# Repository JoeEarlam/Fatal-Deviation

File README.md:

# Fatal Deviation

Fatal Deviation is my 1.5KG beetleweight lifter, with independent 4WD and electronic stability control. The name comes from Ireland's first full-length martial arts movie of the same name, which can be found in its entirety on youtube for the morbidly curious.

This repository is not intended to be instructional - this isn't a full open-source project, but a reference for myself and others who want to see how the sausage is made. If you do build your own (or something similar), please let me know, I'd love to see more weird tiny beetleweights on the scene!

For more information on the design and build process, please check out my build thread: https://forum.bristolbotbuilders.com/t/fatal-deviation-my-over-engineered-beetleweight/232

TPU front end, the night before Bristol Bot Builders' Summer Showdown, July 2025

Steel front end, for Robodojo, May 2025

## Design Criteria and Overview

I impulse bought a TIG welder in Lidl and needed more excuses to use it. Somebody on the internet said that it wasn't possible to build a somewhat competitive beetleweight robot almost entirely from steel. Together, that was all the motivation I needed. Watching fast lifter/grappler bots like P1, Whiplash, Claw Viper/Red Storm, and having previous experience racing RC cars, I knew how I wanted the bot to drive - fast, agile, predictable. This gave me some design requirements:

* Extremely compact chassis to allow as much armour coverage as possible.
* Four independently controlled drive motors, for redundancy and torque vectoring.
* Small, compact and powerful lifter mechanism.
* As much RGB as possible while still having enough power left over for the bot to drive.

## Mechanical Design

The mechanical design uses a welded 304 stainless steel chassis tub - 2mm sides and bottom, with 4mm front and rear sections. Stainless was chosen for aesthetic reasons, and because 2mm hardox is very difficult to source.

The wedge is soft-mounted via threaded aluminium inserts pressed into TPU brackets. The tub protects a TPU clamshell that sandwiches the internal components together, via long screws and threaded inserts to pull it together. Self-tapping screws are used to hold the clamshell into the chassis tub which suspends all the internal components and hopefully provides some shock absorption.

The TPU clamshell design means all the internal components of the robot can be removed as a unit for repair on the bench. Accessing any component only takes a couple of minutes, although unfortunately due to the compact design many connections have to be soldered rather than connectorised/

## Electronic Design

The only way to cram electronics into the remaining space inside the bot is to integrate every function (aside from the receiver) into a single PCB. In approximately 50x70mm total board area, the PCB provides:

* Seeed Xiao RP2040 microcontroller
* 4x 6A drive channels (TI DRV8256P drivers), with current sensing.
* MPU6050 gyro + accelerometer
* IBUS receiver compatible
* Servo power and signal pads
* 7x WS2812 RGB LEDs

The four layer PCB was designed with heavy usage of copper pours, optimised to keep resistance (both electrical and thermal) and inductance as low as possible when using cheap 1oz copper fabrication processes (2oz often costs 3-4 as much as 1oz!). The design also keeps the hot and EMI-prone motor drivers and servo power pads far away from the sensitive IMU and MCU. While only supposed to run 2-3 minutes at a time for events, it's been stress tested with 5-10 minutes of continuous running and barely rises over 45c, even with no airflow and four hot motors spinning inside the bot.

## Software Design

The software is written in Arduino IDE, utilising both cores of the RP2040 microcontroller. The firmware uses the wonderful [TaskScheduler](https://github.com/arkhipenko/TaskScheduler) library by arkhipenko to handle timing and looping, with modularity provided by custom classes containing motor driver logic, IMU data processing, and drive maths. The task-based asynchronous code allows predictable timing for data acquisition and filter functions, while also optimising for minimum latency by triggering drive maths routines the instant that a new radio packet is received.

IMU gyroscope data is used, in combination with the steering channel data received from the RC transmitter, as the input and target variables of a PID loop, which provides the electronic stability control - the bot will steer to self correct back to its intended course if disrupted; either by a bump in the floor or contact with another robot, and allows the bot to hold dead straight line acceleration or smooth drifts on low-friction surfaces where it would otherwise spin out uncontrollably. To improve the turning radius (which is otherwise somewhat poor due to the long aspect ratio of the bot) the front inside wheel is braked on sharp turns, while the rear inside wheel coasts, shifting the centre of rotation for the bot forwards.

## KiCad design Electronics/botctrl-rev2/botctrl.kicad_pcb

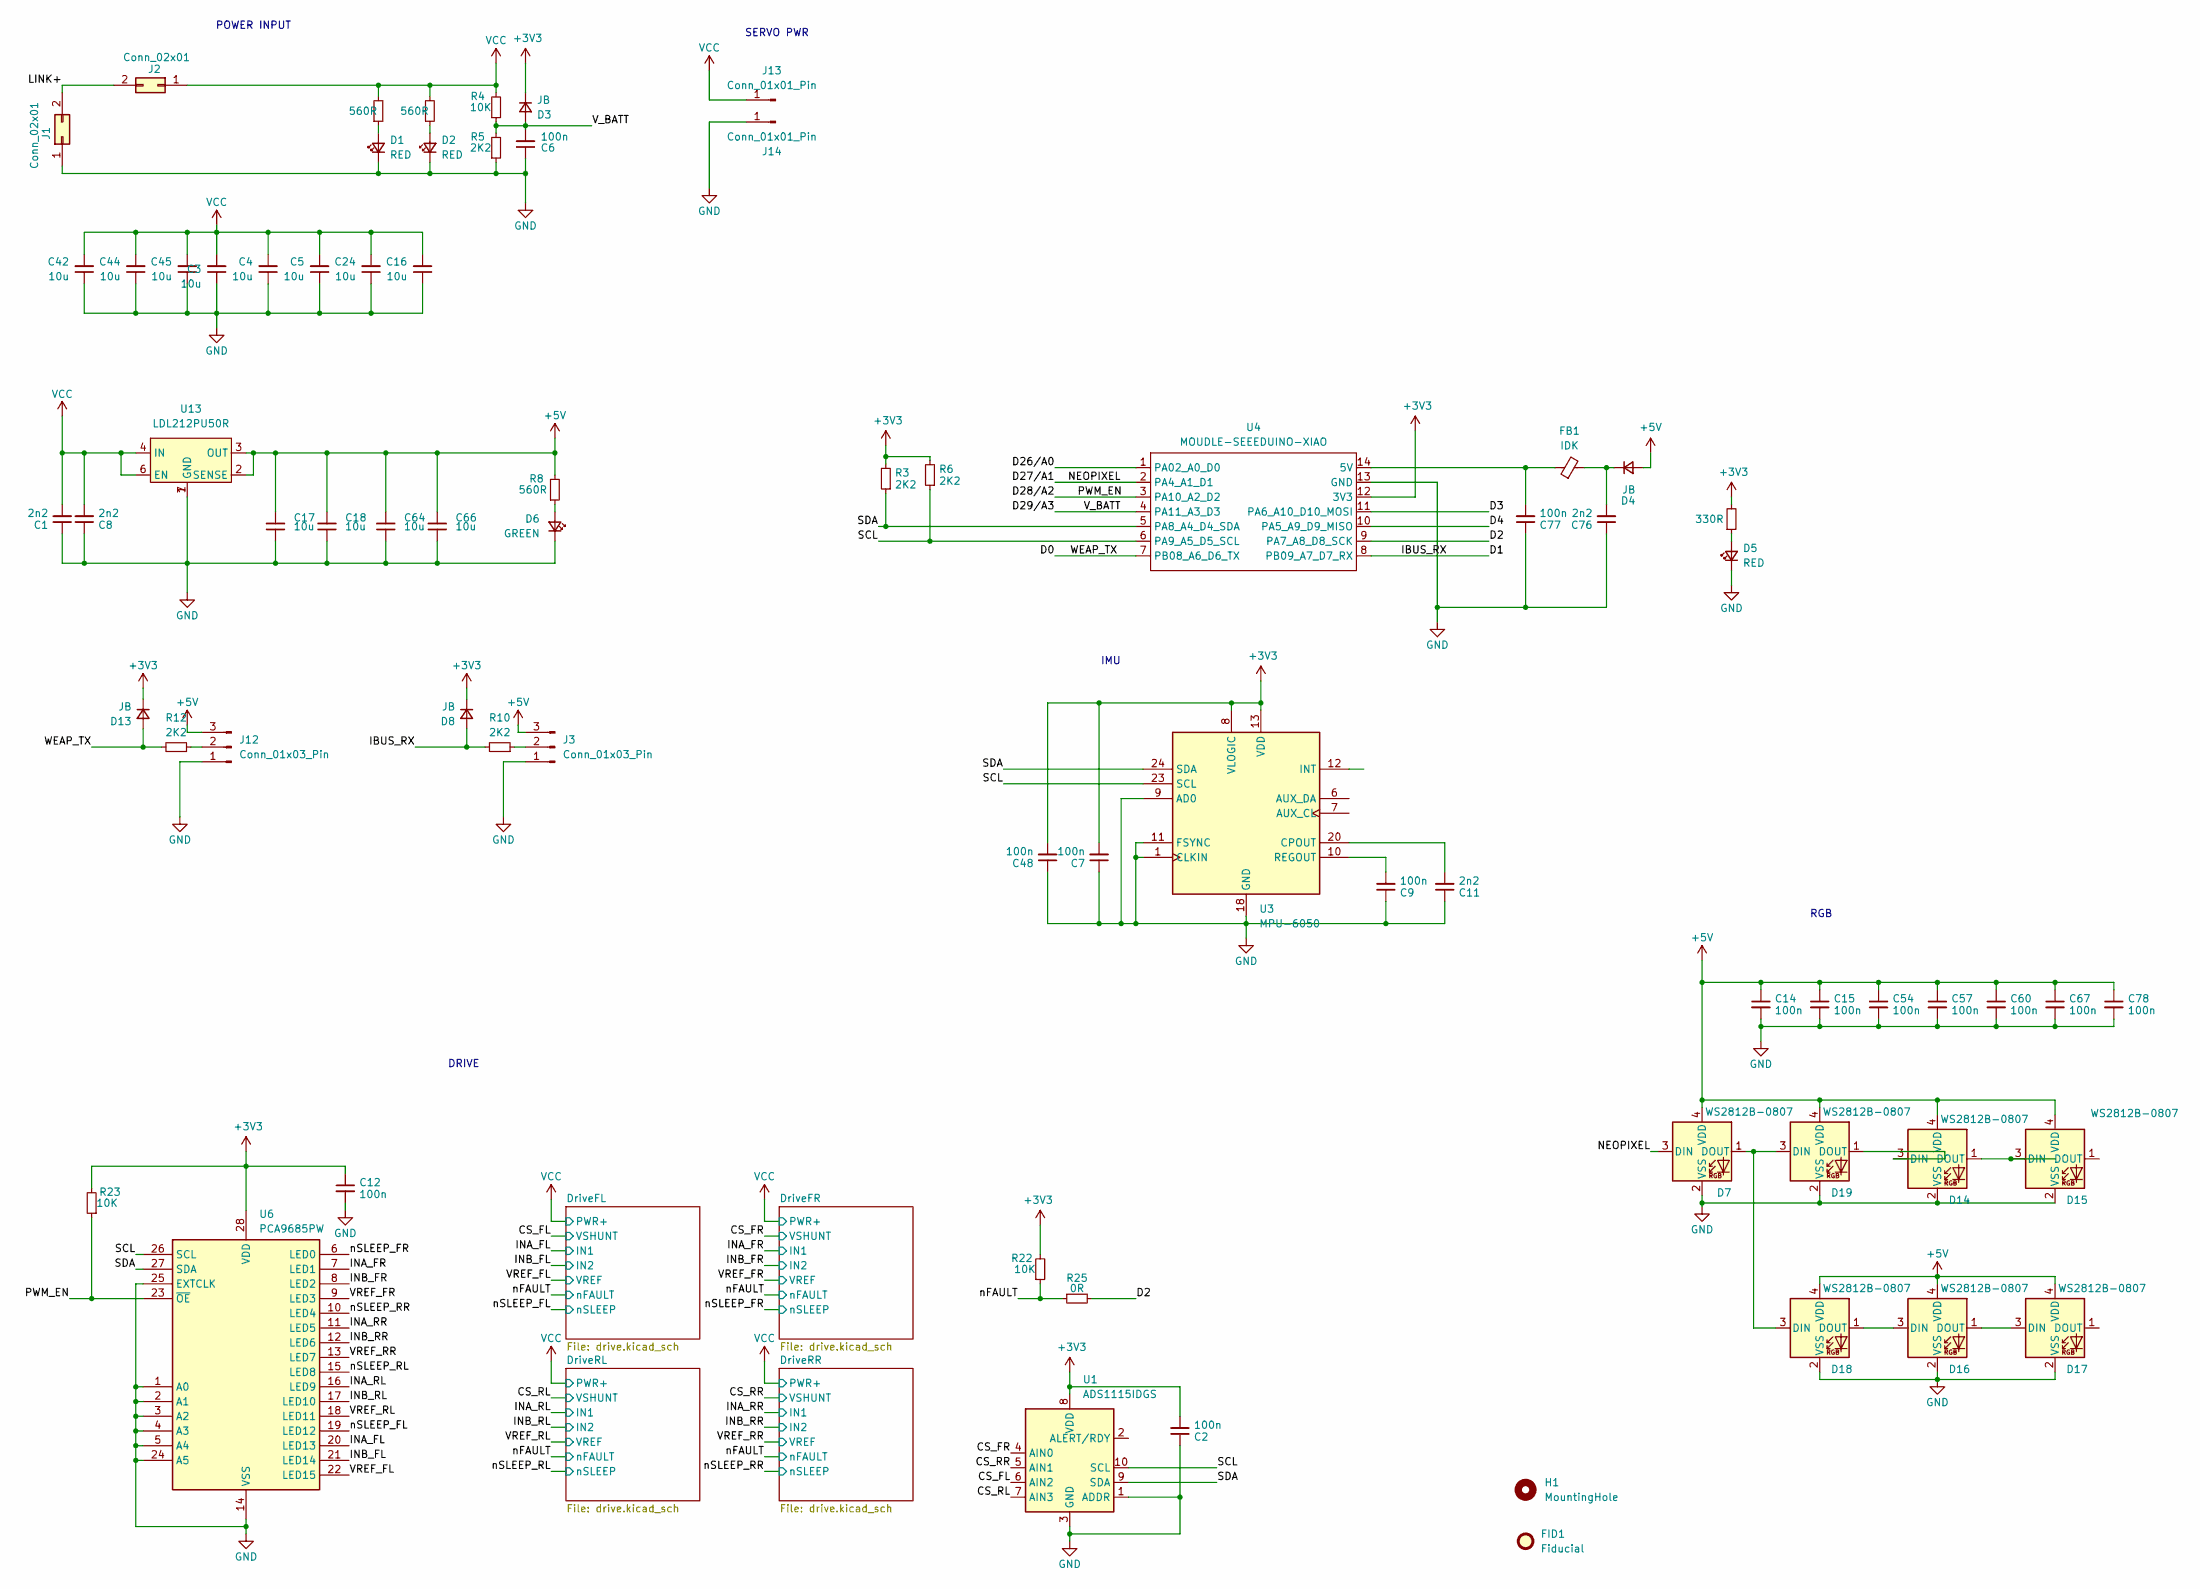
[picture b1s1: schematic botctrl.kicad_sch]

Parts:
C1, C8, C11, C76: 2n2; C_0603_1608Metric
C2, C6, C7, C9, C12, C14, C15, C48, C54, C57, C60, C67, C77, C78: 100n; C_0603_1608Metric
C3, C4, C5, C16, C17, C18, C24, C42, C44, C45, C64, C66: 10u; C_1206_3216Metric
D1, D2: RED; LED_Kingbright_APFA3010_3x1.5mm_Horizontal
D3, D4, D8, D13: JB; D_0603_1608Metric
D5: RED; D_0603_1608Metric
D6: GREEN; D_0603_1608Metric
D7, D14, D15, D16, D17, D18, D19: WS2812B-0807; WS2812-0807
FB1: IDK; L_0603_1608Metric; Part Number 0R
FID1: Fiducial; el-botto
H1: MountingHole; MountingHole_4.3mm_M4_DIN965
J1, J2: Conn_02x01; SolderWire-0.75sqmm_1x02_P4.8mm_D1.25mm_OD2.3mm
J3, J12: Conn_01x03_Pin; SolderWire-0.127sqmm_1x03_P3.7mm_D0.48mm_OD1mm
J13, J14: Conn_01x01_Pin; SolderWire-0.25sqmm_1x01_D0.65mm_OD1.7mm
R1, R2, R8: 560R; R_0603_1608Metric
R3, R5, R6, R10, R12: 2K2; R_0603_1608Metric
R4, R22, R23: 10K; R_0603_1608Metric
R7: 330R; R_0603_1608Metric
R25: 0R; R_0603_1608Metric
U1: ADS1115IDGS; TSSOP-10_3x3mm_P0.5mm
U3: MPU-6050; InvenSense_QFN-24_4x4mm_P0.5mm
U4: MOUDLE-SEEEDUINO-XIAO; MOUDLE14P-SMD-2.54-21X17.8MM
U6: PCA9685PW; TSSOP-28_4.4x9.7mm_P0.65mm
U13: LDL212PU50R; DFN-6-1EP_3x3mm_P0.95mm_EP1.7x2.6mm

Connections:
+3V3: C2.2, C7.2, C12.1, C48.2, D3.1 (K), D8.1 (K), D13.1 (K), R3.2, R6.2, R7.2, R22.2, R23.2, U1.8 (VDD), U3.8 (VLOGIC), U3.13 (VDD), U4.12 (3V3), U6.28 (VDD)
+5V: C14.1, C15.1, C17.2, C18.2, C54.1, C57.1, C60.1, C64.2, C66.2, C67.1, C78.1, D4.2 (A), D7.4 (VDD), D14.4 (VDD), D15.4 (VDD), D16.4 (VDD), D17.4 (VDD), D18.4 (VDD), D19.4 (VDD), J3.3, J12.3, R8.2, U13.2 (SENSE), U13.3 (OUT)
/CS_FL: U1.6 (AIN2); also elsewhere on the board
/CS_FR: U1.4 (AIN0); also elsewhere on the board
/CS_RL: U1.7 (AIN3); also elsewhere on the board
/CS_RR: U1.5 (AIN1); also elsewhere on the board
/D0: D13.2 (A), R12.2, U4.7 (PB08_A6_D6_TX)
/D1: D8.2 (A), R10.2, U4.8 (PB09_A7_D7_RX)
/D2: R25.2, U4.9 (PA7_A8_D8_SCK)
/D3: U4.11 (PA6_A10_D10_MOSI)
/D4: U4.10 (PA5_A9_D9_MISO)
/D26/A0: U4.1 (PA02_A0_D0)
/D27/A1: D7.3 (DIN), U4.2 (PA4_A1_D1)
/D28/A2: R23.1, U4.3 (PA10_A2_D2), U6.23 (~OE)
/D29/A3: C6.2, D3.2 (A), R4.1, R5.2, U4.4 (PA11_A3_D3)
/INA_FL: U6.20 (LED13); also elsewhere on the board
/INA_FR: U6.7 (LED1); also elsewhere on the board
/INA_RL: U6.16 (LED9); also elsewhere on the board
/INA_RR: U6.11 (LED5); also elsewhere on the board
/INB_FL: U6.21 (LED14); also elsewhere on the board
/INB_FR: U6.8 (LED2); also elsewhere on the board
/INB_RL: U6.17 (LED10); also elsewhere on the board
/INB_RR: U6.12 (LED6); also elsewhere on the board
/LINK+: J1.2, J2.2
/SCL: R6.1, U1.10 (SCL), U3.23 (SCL), U4.6 (PA9_A5_D5_SCL), U6.26 (SCL)
/SDA: R3.1, U1.9 (SDA), U3.24 (SDA), U4.5 (PA8_A4_D4_SDA), U6.27 (SDA)
/VREF_FL: U6.22 (LED15); also elsewhere on the board
/VREF_FR: U6.9 (LED3); also elsewhere on the board
/VREF_RL: U6.18 (LED11); also elsewhere on the board
/VREF_RR: U6.13 (LED7); also elsewhere on the board
/nFAULT: R22.1, R25.1; also elsewhere on the board
/nSLEEP_FL: U6.19 (LED12); also elsewhere on the board
/nSLEEP_FR: U6.6 (LED0); also elsewhere on the board
/nSLEEP_RL: U6.15 (LED8); also elsewhere on the board
/nSLEEP_RR: U6.10 (LED4); also elsewhere on the board
GND: C1.1, C2.1, C3.1, C4.1, C5.1, C6.1, C7.1, C8.1, C9.1, C11.1, C12.2, C14.2, C15.2, C16.1, C17.1, C18.1, C24.1, C42.1, C44.1, C45.1, C48.1, C54.2, C57.2, C60.2, C64.1, C66.1, C67.2, C76.1, C77.1, C78.2, D1.1 (K), D2.1 (K), D5.1 (K), D6.1 (K), D7.2 (VSS), D14.2 (VSS), D15.2 (VSS), D16.2 (VSS), D17.2 (VSS), D18.2 (VSS), D19.2 (VSS), J1.1, J3.1, J12.1, J14.1, R5.1, U1.1 (ADDR), U1.3 (GND), U3.1 (CLKIN), U3.9 (AD0), U3.11 (FSYNC), U3.18 (GND), U4.13 (GND), U6.1 (A0), U6.2 (A1), U6.3 (A2), U6.4 (A3), U6.5 (A4), U6.14 (VSS), U6.24 (A5), U6.25 (EXTCLK), U13.1 (GND), U13.7 (GND); also elsewhere on the board
unnamed: D1.2 (A), R1.1
unnamed: D2.2 (A), R2.1
unnamed: C76.2, D4.1 (K), FB1.2
unnamed: D5.2 (A), R7.1
unnamed: D6.2 (A), R8.1
unnamed: D14.3 (DIN), D19.1 (DOUT)
unnamed: D14.1 (DOUT), D15.3 (DIN)
unnamed: D16.3 (DIN), D18.1 (DOUT)
unnamed: D16.1 (DOUT), D17.3 (DIN)
unnamed: D7.1 (DOUT), D18.3 (DIN), D19.3 (DIN)
unnamed: J3.2, R10.1
unnamed: J12.2, R12.1
unnamed: C11.2, U3.20 (CPOUT)
unnamed: C9.2, U3.10 (REGOUT)
unnamed: C77.2, FB1.1, U4.14 (5V)
VCC: C1.2, C3.2, C4.2, C5.2, C8.2, C16.2, C24.2, C42.2, C44.2, C45.2, J2.1, J13.1, R1.2, R2.2, R4.2, U13.4 (IN), U13.6 (EN); also elsewhere on the board

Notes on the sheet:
DRIVE
POWER INPUT
SERVO PWR
IMU
RGB

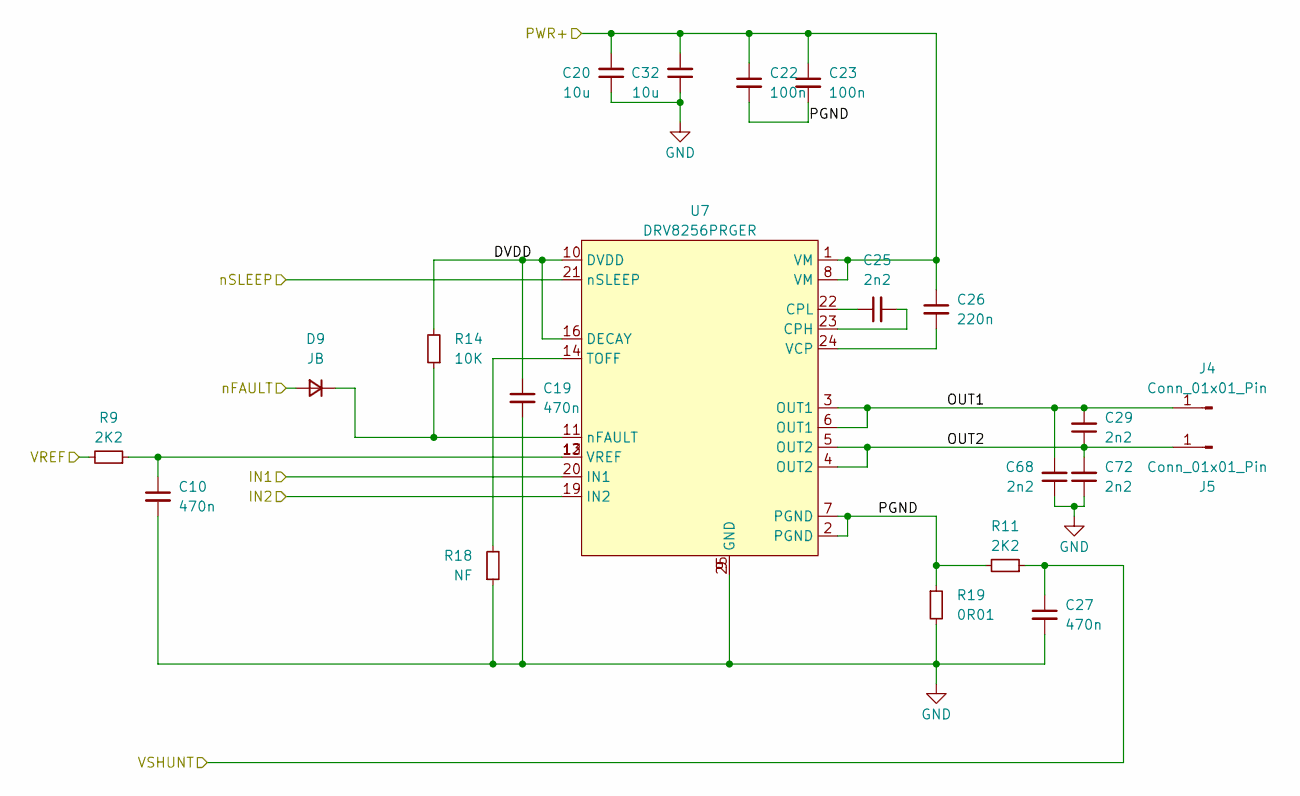
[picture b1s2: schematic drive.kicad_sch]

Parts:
C10, C19, C27: 470n; C_0603_1608Metric
C20, C32: 10u; C_1206_3216Metric
C22, C23: 100n; C_0603_1608Metric
C25, C29, C68, C72: 2n2; C_0603_1608Metric
C26: 220n; C_0603_1608Metric
D9: JB; D_0603_1608Metric
J4, J5: Conn_01x01_Pin; SolderWire-0.25sqmm_1x01_D0.65mm_OD1.7mm
R9, R11: 2K2; R_0603_1608Metric
R14: 10K; R_0603_1608Metric
R18: NF; R_0603_1608Metric
R19: 0R01; R_1210_3225Metric
U7: DRV8256PRGER; VQFN-24-1EP_4x4mm_P0.5mm_EP2.45x2.45mm_ThermalVias

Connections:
/CS_FL: C27.1, R11.1; also elsewhere on the board
/DriveFL/DVDD: C19.1, R14.2, U7.10 (DVDD), U7.16 (DECAY)
/DriveFL/OUT1: C29.2, C68.2, J4.1, U7.3 (OUT1), U7.6 (OUT1)
/DriveFL/OUT2: C29.1, C72.2, J5.1, U7.4 (OUT2), U7.5 (OUT2)
/DriveFL/PGND: C22.2, C23.2, R11.2, R19.1, U7.2 (PGND), U7.7 (PGND)
/INA_FL: U7.20 (IN1); also elsewhere on the board
/INB_FL: U7.19 (IN2); also elsewhere on the board
/VREF_FL: R9.2; also elsewhere on the board
/nFAULT: D9.2 (A); also elsewhere on the board
/nSLEEP_FL: U7.21 (nSLEEP); also elsewhere on the board
GND: C10.2, C19.2, C20.1, C27.2, C32.1, C68.1, C72.1, R18.1, R19.2, U7.9 (GND), U7.25 (GND); also elsewhere on the board
unnamed: C10.1, R9.1, U7.12 (VREF), U7.13 (VREF)
unnamed: D9.1 (K), R14.1, U7.11 (nFAULT)
unnamed: C25.2, U7.23 (CPH)
unnamed: C25.1, U7.22 (CPL)
unnamed: R18.2, U7.14 (TOFF)
unnamed: C26.2, U7.24 (VCP)
VCC: C20.2, C22.1, C23.1, C26.1, C32.2, U7.1 (VM), U7.8 (VM); also elsewhere on the board

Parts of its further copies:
C13, C31, C39, C43, C51, C52, C55, C56, C63: 470n; C_0603_1608Metric
C21, C28, C30, C33, C36, C40: 10u; C_1206_3216Metric
C34, C35, C46, C47, C58, C59: 100n; C_0603_1608Metric
C37, C41, C49, C53, C61, C65, C69, C70, C71, C73, C74, C75: 2n2; C_0603_1608Metric
C38, C50, C62: 220n; C_0603_1608Metric
D10, D11, D12: JB; D_0603_1608Metric
J6, J7, J8, J9, J10, J11: Conn_01x01_Pin; SolderWire-0.25sqmm_1x01_D0.65mm_OD1.7mm
R13, R15, R16, R17, R20, R21: 2K2; R_0603_1608Metric
R24, R34, R44: 10K; R_0603_1608Metric
R28, R38, R48: NF; R_0603_1608Metric
R29, R39, R49: 0R01; R_1210_3225Metric
U8, U9, U10: DRV8256PRGER; VQFN-24-1EP_4x4mm_P0.5mm_EP2.45x2.45mm_ThermalVias

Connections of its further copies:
/CS_FR: C39.1, R17.1; also elsewhere on the board
/CS_RL: C51.1, R20.1; also elsewhere on the board
/CS_RR: C63.1, R21.1; also elsewhere on the board
/DriveFR/DVDD: C31.1, R24.2, U8.10 (DVDD), U8.16 (DECAY)
/DriveFR/OUT1: C41.2, C69.2, J6.1, U8.3 (OUT1), U8.6 (OUT1)
/DriveFR/OUT2: C41.1, C73.2, J7.1, U8.4 (OUT2), U8.5 (OUT2)
/DriveFR/PGND: C34.2, C35.2, R17.2, R29.1, U8.2 (PGND), U8.7 (PGND)
/DriveRL/DVDD: C43.1, R34.2, U9.10 (DVDD), U9.16 (DECAY)
/DriveRL/OUT1: C53.2, C70.2, J8.1, U9.3 (OUT1), U9.6 (OUT1)
/DriveRL/OUT2: C53.1, C74.2, J9.1, U9.4 (OUT2), U9.5 (OUT2)
/DriveRL/PGND: C46.2, C47.2, R20.2, R39.1, U9.2 (PGND), U9.7 (PGND)
/DriveRR/DVDD: C55.1, R44.2, U10.10 (DVDD), U10.16 (DECAY)
/DriveRR/OUT1: C65.2, C71.2, J10.1, U10.3 (OUT1), U10.6 (OUT1)
/DriveRR/OUT2: C65.1, C75.2, J11.1, U10.4 (OUT2), U10.5 (OUT2)
/DriveRR/PGND: C58.2, C59.2, R21.2, R49.1, U10.2 (PGND), U10.7 (PGND)
/INA_FR: U8.20 (IN1); also elsewhere on the board
/INA_RL: U9.20 (IN1); also elsewhere on the board
/INA_RR: U10.20 (IN1); also elsewhere on the board
/INB_FR: U8.19 (IN2); also elsewhere on the board
/INB_RL: U9.19 (IN2); also elsewhere on the board
/INB_RR: U10.19 (IN2); also elsewhere on the board
/VREF_FR: R13.2; also elsewhere on the board
/VREF_RL: R15.2; also elsewhere on the board
/VREF_RR: R16.2; also elsewhere on the board
/nFAULT: D10.2 (A), D11.2 (A), D12.2 (A); also elsewhere on the board
/nSLEEP_FR: U8.21 (nSLEEP); also elsewhere on the board
/nSLEEP_RL: U9.21 (nSLEEP); also elsewhere on the board
/nSLEEP_RR: U10.21 (nSLEEP); also elsewhere on the board
GND: C13.2, C21.1, C28.1, C30.1, C31.2, C33.1, C36.1, C39.2, C40.1, C43.2, C51.2, C52.2, C55.2, C56.2, C63.2, C69.1, C70.1, C71.1, C73.1, C74.1, C75.1, R28.1, R29.2, R38.1, R39.2, R48.1, R49.2, U8.9 (GND), U8.25 (GND), U9.9 (GND), U9.25 (GND), U10.9 (GND), U10.25 (GND); also elsewhere on the board
unnamed: C13.1, R13.1, U8.12 (VREF), U8.13 (VREF)
unnamed: C52.1, R15.1, U9.12 (VREF), U9.13 (VREF)
unnamed: C56.1, R16.1, U10.12 (VREF), U10.13 (VREF)
unnamed: D10.1 (K), R24.1, U8.11 (nFAULT)
unnamed: D11.1 (K), R34.1, U9.11 (nFAULT)
unnamed: D12.1 (K), R44.1, U10.11 (nFAULT)
unnamed: C37.2, U8.23 (CPH)
unnamed: C37.1, U8.22 (CPL)
unnamed: R28.2, U8.14 (TOFF)
unnamed: C38.2, U8.24 (VCP)
unnamed: C49.2, U9.23 (CPH)
unnamed: C49.1, U9.22 (CPL)
unnamed: R38.2, U9.14 (TOFF)
unnamed: C50.2, U9.24 (VCP)
unnamed: C61.2, U10.23 (CPH)
unnamed: C61.1, U10.22 (CPL)
unnamed: R48.2, U10.14 (TOFF)
unnamed: C62.2, U10.24 (VCP)
VCC: C21.2, C28.2, C30.2, C33.2, C34.1, C35.1, C36.2, C38.1, C40.2, C46.1, C47.1, C50.1, C58.1, C59.1, C62.1, U8.1 (VM), U8.8 (VM), U9.1 (VM), U9.8 (VM), U10.1 (VM), U10.8 (VM); also elsewhere on the board

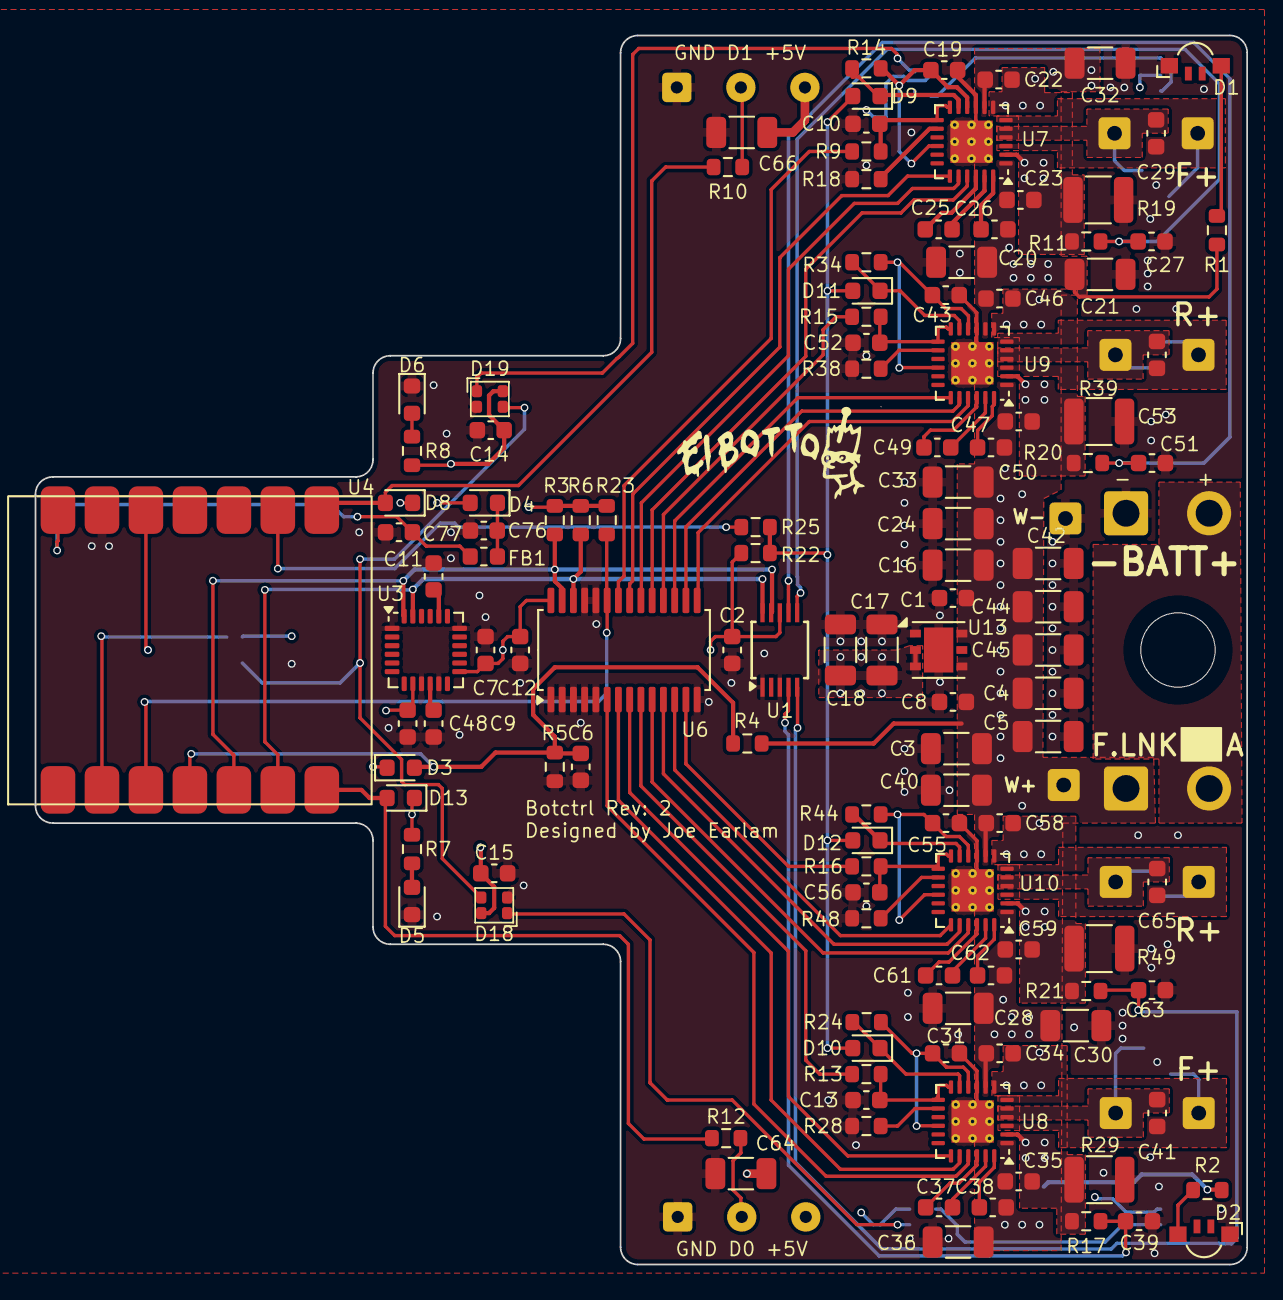
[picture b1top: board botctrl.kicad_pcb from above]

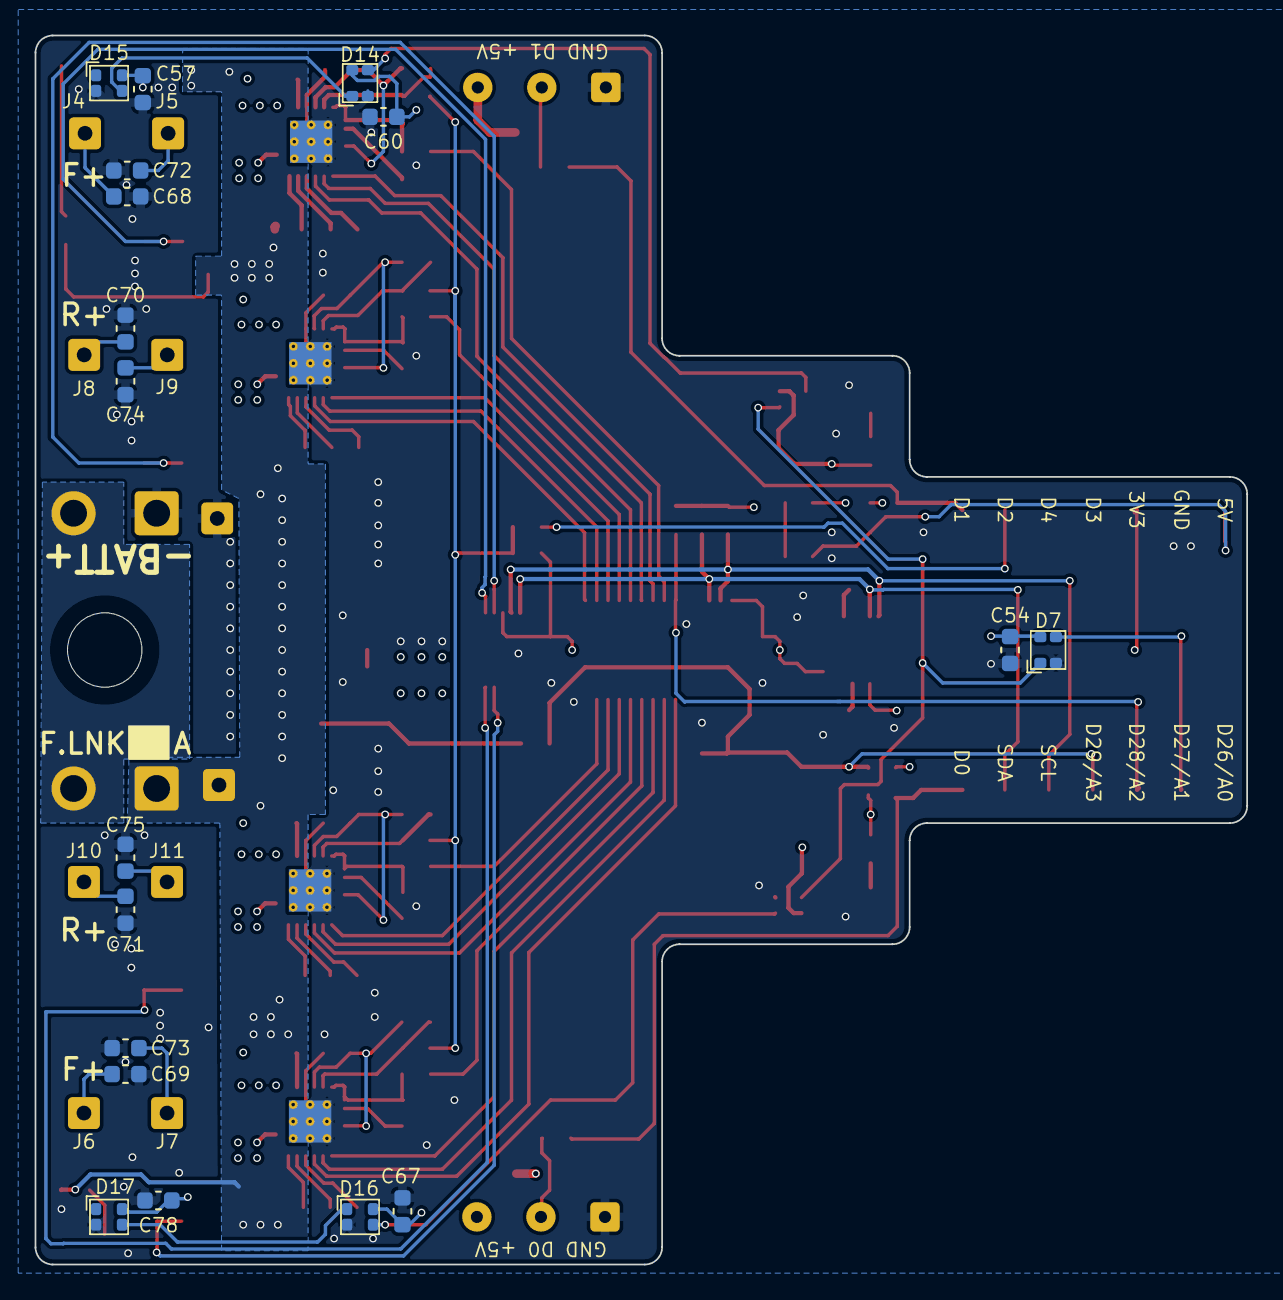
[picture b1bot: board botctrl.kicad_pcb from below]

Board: 4 copper layers, 70.0 x 71.0 mm, 156 parts (18 on the bottom side), 89 nets.

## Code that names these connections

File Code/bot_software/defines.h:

#ifndef DEFINES_H
#define DEFINES_H

//pins
#define PIN_WEAP 0
#define PIN_IBUS 1
#define PIN_DRV_FAULT 2
#define PIN_NEO_BRD 27
#define PIN_NEO_PWR 11
#define PIN_NEO_XIAO 12
#define PIN_PWM_EN 28
#define PIN_V_BATT A3

//PWM output channels
#define NSLEEP_FL 0
#define INA_FL 1
#define INB_FL 2
#define VREF_FL 3

#define NSLEEP_RL 4
#define INA_RL 5
#define INB_RL 6
#define VREF_RL 7

#define NSLEEP_RR 8
#define INA_RR 10
#define INB_RR 9
#define VREF_RR 11

#define NSLEEP_FR 12
#define INA_FR 14
#define INB_FR 13
#define VREF_FR 15

//misc
#define LED_COUNT 4
#define RGB_SPEED 16
#define IBUS_PERIOD 7
#define LOW_BATT_VOLTS 9.5

#endif

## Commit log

2025-02-23 removed out of date step files
2025-02-23 documentation fix
2025-02-23 added credit for broken IMU filter
2025-07-29 updated to latest version
